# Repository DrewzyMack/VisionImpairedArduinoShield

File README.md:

# Vision Impaired Arduino Shield
An Arduino Shield designed for a vision impaired student in my robotics class.

## General Info
This was designed for a vision impaired student in my robotics class, as we decided the pin spacing on an Arduino was too close together.

Feel free to download the EAGLE files and customise it however you like.

If you just want to get one made, download the GERBER .zip file and send it right off to your preferred PCB manufacturer. (I used JLCPCB and got it made in their white soldermask with a black silkscreen to maximise contrast)

## Bill of Materials
| Part                      | Quantity | Notes                                 |
|---------------------------|----------|---------------------------------------|
| 1x2 Female Pin Header     | 24       |                                       |
| 1x3 Female Pin Header     | 3        |                                       |
| 1x10 Female Pin Header    | 2        |                                       |
| 1x32 Male Pin Header      | 1        | Broken into lengths of 10, 8, 8 and 6 |
| 12mm Tactile Switch       | 1        |                                       |

## Images

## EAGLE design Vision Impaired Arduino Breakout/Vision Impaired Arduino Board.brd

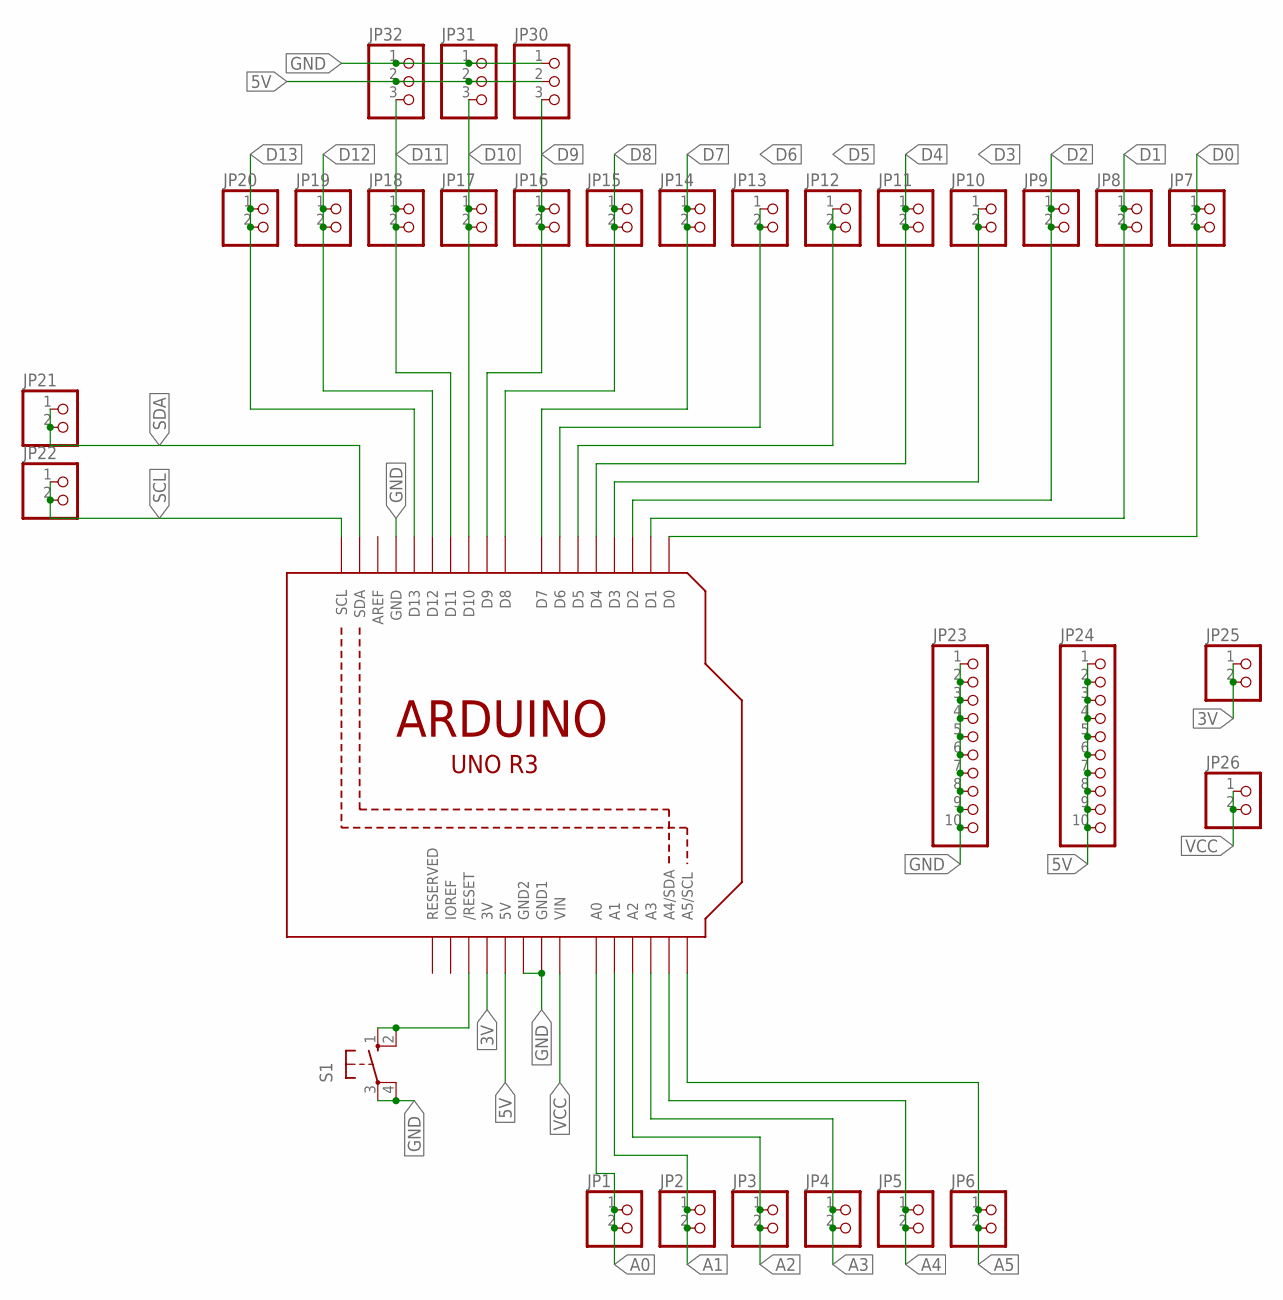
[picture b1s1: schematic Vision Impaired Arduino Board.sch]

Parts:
JP1, JP2, JP3, JP4, JP5, JP6, JP7, JP8, JP9, JP10, JP11, JP12, JP13, JP14, JP15, JP16, JP17, JP18, JP19, JP20, JP21, JP22, JP25, JP26: PINHD-1X2; 1X02
JP23, JP24: PINHD-1X10; 1X10
JP30, JP31, JP32: PINHD-1X3; 1X03
S1: 40-XX; B3F-40XX
U1: ARDUINOR3-BPLACE

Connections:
3V: JP25.1, JP25.2, U1.3V
5V: JP24.1, JP24.2, JP24.3, JP24.4, JP24.5, JP24.6, JP24.7, JP24.8, JP24.9, JP24.10, JP30.2, JP31.2, JP32.2, U1.5V
A0: JP1.1, JP1.2, U1.A0
A1: JP2.1, JP2.2, U1.A1
A2: JP3.1, JP3.2, U1.A2
A3: JP4.1, JP4.2, U1.A3
A4: JP5.1, JP5.2, U1.A4 (A4/SDA)
A5: JP6.1, JP6.2, U1.A5 (A5/SCL)
D0: JP7.1, JP7.2, U1.D0
D1: JP8.1, JP8.2, U1.D1
D2: JP9.1, JP9.2, U1.D2
D3: JP10.1, JP10.2, U1.D3
D4: JP11.1, JP11.2, U1.D4
D5: JP12.1, JP12.2, U1.D5
D6: JP13.1, JP13.2, U1.D6
D7: JP14.1, JP14.2, U1.D7
D8: JP15.1, JP15.2, U1.D8
D9: JP16.1, JP16.2, JP30.3, U1.D9
D10: JP17.1, JP17.2, JP31.3, U1.D10
D11: JP18.1, JP18.2, JP32.3, U1.D11
D12: JP19.1, JP19.2, U1.D12
D13: JP20.1, JP20.2, U1.D13
GND: JP23.1, JP23.2, JP23.3, JP23.4, JP23.5, JP23.6, JP23.7, JP23.8, JP23.9, JP23.10, JP30.1, JP31.1, JP32.1, S1.3, S1.4 (P1), U1.GND, U1.GND1, U1.GND2
unnamed: S1.1 (S), S1.2 (S1), U1.RESET (/RESET)
SCL: JP22.1, JP22.2, U1.SCL
SDA: JP21.1, JP21.2, U1.SDA
VCC: JP26.1, JP26.2, U1.VIN

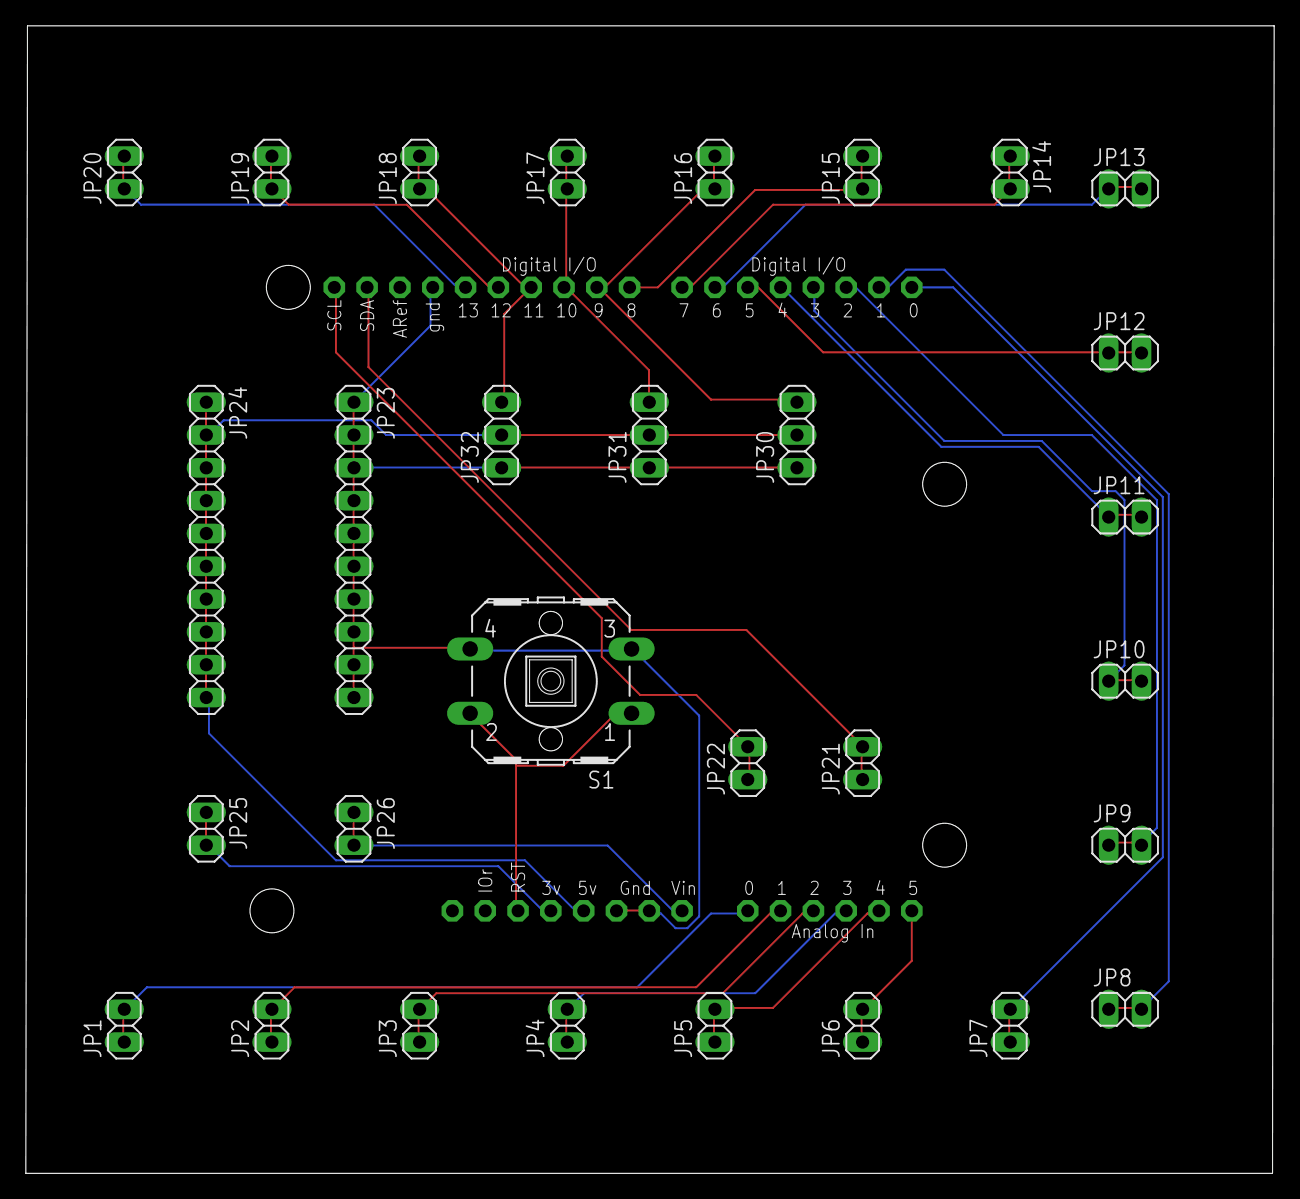
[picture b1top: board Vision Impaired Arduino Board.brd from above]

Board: 2 copper layers, 96.6 x 88.8 mm, 31 parts (0 on the bottom side), 27 nets.

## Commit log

2023-06-27 Cropped board images
2023-06-27 updated image names and readme
2023-06-27 Added Eagle & Gerber Files
